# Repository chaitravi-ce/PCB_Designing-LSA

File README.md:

# PCB_Designing-LSA

## A PCB Design for Line Sensor Array(LSA) with 4 sensors

## Software Used

> Designed using kiCAD Software.
> To download the software visit : https://kicad.org

## Design

* It is a single layered board. 

* Front View of the Board

* Bottom View of the Board

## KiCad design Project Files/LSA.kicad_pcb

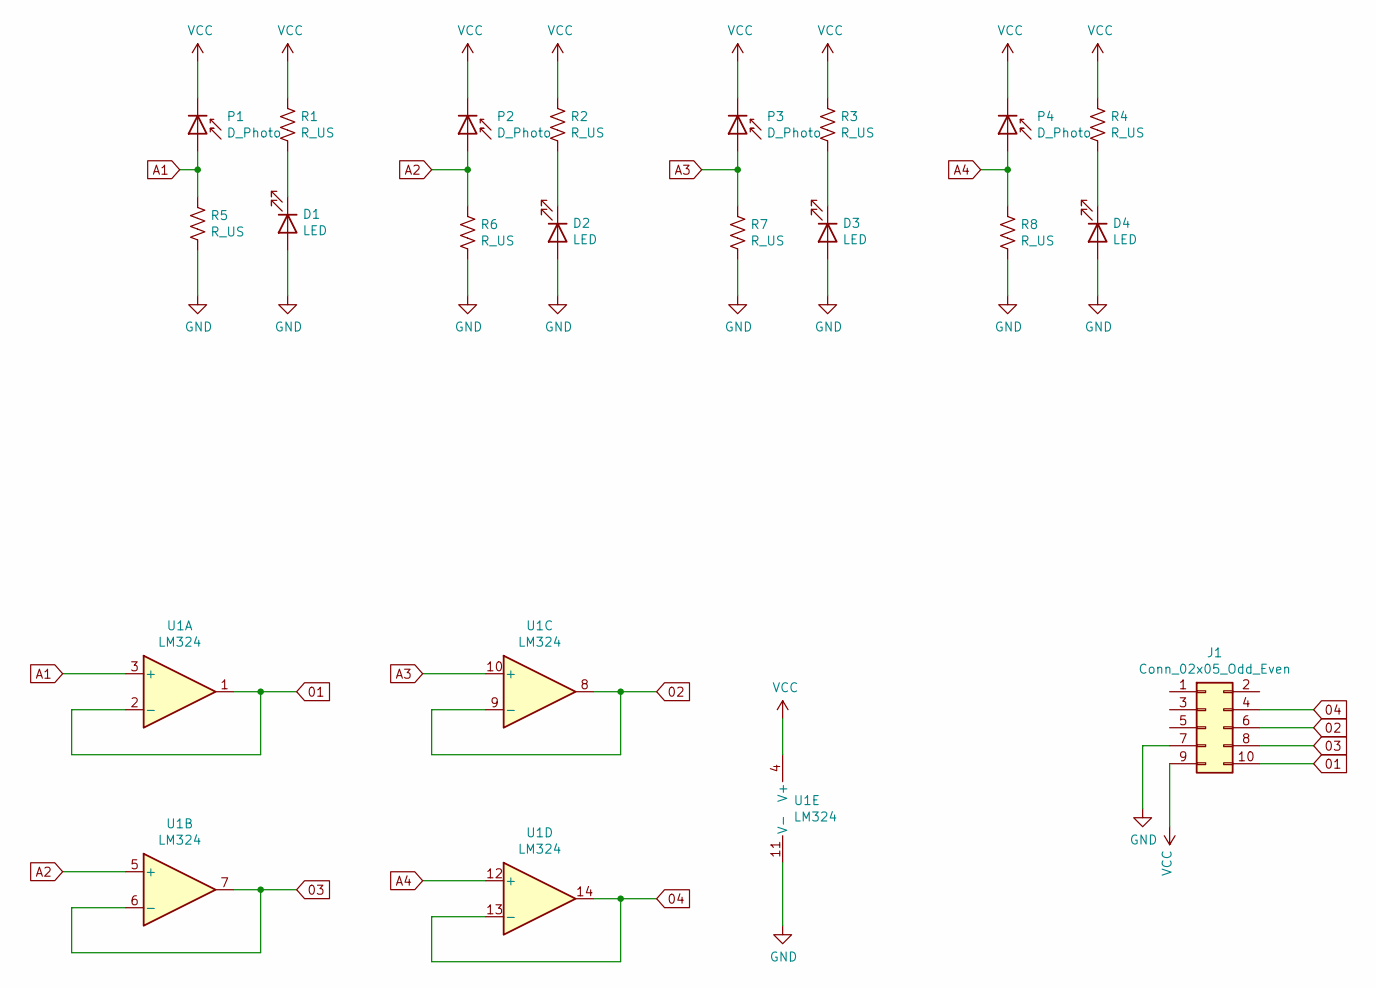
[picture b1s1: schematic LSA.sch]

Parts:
D1, D2, D3, D4: LED; LED_D3.0mm_IRBlack
J1: Conn_02x05_Odd_Even; IDC-Header_2x05_P2.54mm_Vertical
P1, P2, P3, P4: D_Photo; LED_D5.0mm
R1, R2, R3, R4, R5, R6, R7, R8: R_US; R_Axial_DIN0204_L3.6mm_D1.6mm_P5.08mm_Horizontal
U1: LM324; DIP-14_W7.62mm

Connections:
01: J1.10, U1.1, U1.2 (-)
02: J1.6, U1.8, U1.9 (-)
03: J1.8, U1.6 (-), U1.7
04: J1.4, U1.13 (-), U1.14
A1: P1.2 (A), R5.1, U1.3 (+)
A2: P2.2 (A), R6.1, U1.5 (+)
A3: P3.2 (A), R7.1, U1.10 (+)
A4: P4.2 (A), R8.1, U1.12 (+)
GND: D1.2 (A), D2.2 (A), D3.2 (A), D4.2 (A), J1.7, R5.2, R6.2, R7.2, R8.2, U1.11 (V-)
unnamed: D1.1 (K), R1.2
unnamed: D2.1 (K), R2.2
unnamed: D3.1 (K), R3.2
unnamed: D4.1 (K), R4.2
VCC: J1.9, P1.1 (K), P2.1 (K), P3.1 (K), P4.1 (K), R1.1, R2.1, R3.1, R4.1, U1.4 (V+)

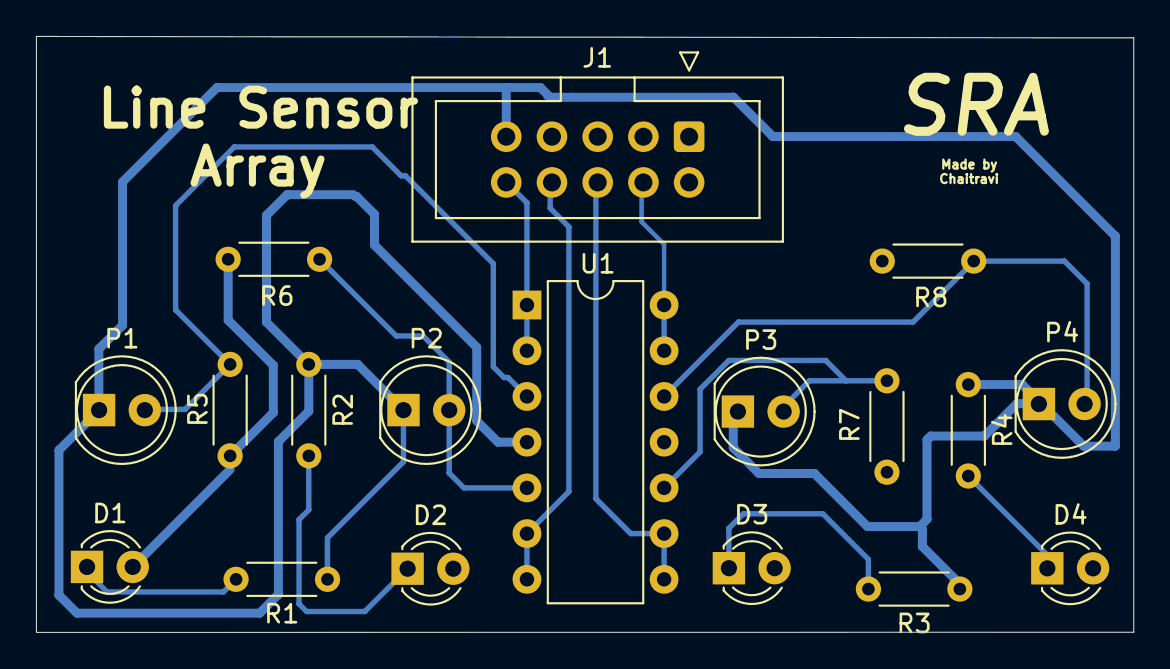
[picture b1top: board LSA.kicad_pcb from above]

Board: 2 copper layers, 61.0 x 33.1 mm, 18 parts (0 on the bottom side), 14 nets.

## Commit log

2021-01-07 Project Files
2021-01-07 Added Assets
